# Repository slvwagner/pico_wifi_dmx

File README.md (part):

# pico_wifi_dmx

WiFi-controlled DMX512 controller firmware and browser UI for the Raspberry Pi Pico 2 W (RP2350). Each Pico drives one full 512-channel DMX universe, and one show can combine multiple named Picos as separate DMX outputs/universes. Fixtures are assigned to their output, so the same DMX address can be reused in different universes. The browser can be used for setup and live editing, while chases and effects can also run autonomously on the involved Picos so show playback does not depend on browser timing or WiFi latency.

- **Latest stable release:** `1.3.0`

See [Versioning](#versioning) for the version-number and branch policy and [CHANGELOG.md](CHANGELOG.md) for release notes.

## Getting Started

For a customer PC running 64-bit Windows, download and run the current
**[WiFiPicoDMX 1.3.0 Windows installer](https://github.com/slvwagner/pico_wifi_dmx/releases/download/v1.3.0/wifi-pico-dmx-1.3.0-windows-x64.exe)**.
The installer includes the customer application, local web server, manual, and
guided Pico firmware updater. Because the current installer is unsigned,
Windows can display a SmartScreen publisher warning.

For a 64-bit Ubuntu or Debian computer, download the
**[WiFiPicoDMX 1.3.0 Debian package](https://github.com/slvwagner/pico_wifi_dmx/releases/download/v1.3.0/wifi-pico-dmx_1.3.0_amd64.deb)**
and install it with `sudo apt install ./wifi-pico-dmx_1.3.0_amd64.deb`.

Read the matching
**[WiFiPicoDMX 1.3.0 user manual (PDF)](https://github.com/slvwagner/pico_wifi_dmx/releases/download/v1.3.0/user-manual.pdf)**
for installation, firmware flashing, show setup, and operation instructions.

The [latest GitHub Release](https://github.com/slvwagner/pico_wifi_dmx/releases/latest)
also provides the installer checksum, Pico firmware images, release manifest,
and PDF user manual.

Continue with [Install the Windows customer application](#install-the-windows-customer-application)
for the complete installation, network-access, firmware-update, and startup
instructions.

## Table of Contents

- [Overview](#overview)
- [Critical XAMPP environment safety](#critical-xampp-environment-safety)
- [Customer installation details](#customer-installation-details)
- [Automated Tests](#automated-tests)
- [Project Structure](#project-structure)
- [Versioning](#versioning)
- [Architecture](#architecture)
- [Playback Modes](#playback-modes)
- [HTTP API](#http-api)
- [Web UI](#web-ui)
- [Detailed Source Reference](#detailed-source-reference)
- [Requirements](#requirements)
- [Configure](#configure)
- [Build](#build)
- [Flash](#flash)
- [Resource Usage](#resource-usage)
- [Notes](#notes)

## Overview

The project combines firmware, a XAMPP-hosted web interface, JSON-based setup storage, and automated tests/documentation for a complete small lighting-control workflow.

Core features:

### Show setup and data

- **Fixture Controller** — define fixture profiles, patch one or many fixtures, edit live values, recall Default/Blackout values, create fixture groups, save scenes, and build reusable palettes.
- **Fixture Library** — load fixture profiles from the converted Open Fixture Library catalog with defaults, fine channels, compatible RGB matrices, advanced multi-emitter colors, split-color and filter previews, capability ranges, highlights, and wheel images; merge edited show profiles with reusable library modes in either direction; and export/import the complete catalog as a compressed ZIP.
- **DMX Outputs** — configure multiple named Pico controllers and universes in one show, discover devices on the network, assign every fixture to an output, reuse DMX addresses across universes, and monitor show-wide Pico availability from the shared header.
- **Portable show and library backups** — Fixture Controller provides separate **Export Show**, **Import Show**, **Export Library**, and **Import Library** actions. The show JSON embeds definitions used by its patched fixtures; the compressed library ZIP contains the complete reusable catalog.
- **Server-side JSON data** — setup data is stored under XAMPP `data/*.json`; the complete setup export collects these stores into one portable backup file.

### Programming and visualization

- **Groups and Group Edit** — select fixtures manually or through saved groups, then edit matching controls across mixed fixture types. Optional **Merge Controls** mode combines matching 8-bit/16-bit functions and RGB/RGBW/RGBWA/CMY/CMYK color controls while retaining each fixture's native channels.
- **Scenes and Palettes** — scenes store complete saved looks for their scope; palettes store partial looks such as positions, colors, gobos, dimmer, beam, or fan-out results. Filled tiles can be renamed and styled with a background color plus an optional visual.
- **Fan Out** — shape selected fixtures around snapshotted base values, including Pan/Tilt fan targets, with affected controls highlighted directly in the controller or chaser step editor.
- **Pixel Matrices** — create logical displays up to 64×64 pixels, map each pixel manually or automatically to fixture RGB/RGBW/RGBWA/CMY/CMYK controls or native matrix pixels, and convert uploaded PNG/JPEG/WebP/GIF pictures in the browser with fit and brightness controls. Controller and Show Run recall pictures across the fixtures' assigned DMX Outputs. Chaser can capture pictures as animated steps, preview them on the primary output, and split an autonomous upload into linked Pico payloads.
- **Room Plane** — calibrated room-plane coordinate mapping for moving-light pan/tilt targeting, with a three-point minimum and optional per-fixture accuracy points, saved plane definitions that preserve every point and its calibration, localized triangle interpolation, group selection, and shared Scene/Palette recalls for checking the programmed look while positioning fixtures.

### Playback and live operation

- **Show Run operator page** — arrange Groups, Fixtures, Scenes, Palettes, Pixel Matrices, Room Planes, Live Controls, masters, MIDI, and Pico playback in a configurable card matrix. Operator-critical cards can be moved into a fixed, independently scrolling single-column sidebar with 1–12 configurable rows. The sidebar uses the same visual design and shared adjustable width as the Controller toolbox rail. Card, sidebar, and tile layouts are saved to the server, cards can be repeated for separate operator banks, and the adaptive sticky header keeps navigation visible while reporting show-wide Pico output health.
- **Shared Toolboxes sidebar** — scenes, groups, palettes, fan out, chases, chase steps, playback, effects, and room-plane tools live in a shared resizable sidebar. A common Edit mode enables touch-friendly toolbox and tile reordering plus Cols/Rows selectors, while width, order, collapse state, and group selection are restored consistently across pages.
- **Chaser** — create step-based chases, define participating controls, add/capture/duplicate/reorder steps, recall or edit saved Pixel Matrix pictures directly in the toolbox, preview recalled chases or individual steps on DMX, use browser playback with direction and ping-pong modes, and upload chases into Pico slots for standalone playback.
- **Effects** — apply circle, figure-8, pan swing, tilt swing, sine, and pulse effects to compatible fixture controls. Effects are relative to the current base/scene value and can be saved as reusable recipes or uploaded to Pico effect slots.
- **Pico Playback** — run chaser and effect slots directly on the Pico with play/stop, state-aware pause/resume, direction, loop and ping-pong modes, BPM/speed changes, and slot status readback. Browser, chaser, effect, and manual-recall handoffs stop conflicting playback engines before changing DMX output.
- **MIDI control** — connect a Web MIDI controller or use the Launch Control XL emulator, learn mappings for scenes, live controls, masters, and Pico playback actions, and use soft takeover for continuous controls.
- **GPIO Control** — choose a configured DMX Output and keep independent Pico GPIO mappings per universe for actions such as chase/effect play, stop, pause, resume, speed, BPM, and tap tempo. ADC-capable pins support smoothed analog speed/BPM control; the complete per-output setup autosaves to XAMPP and the selected mapping can be pushed to or read from its Pico.

### Firmware, diagnostics, and development

- **DMX Buffer Monitor** — select a named DMX Output/universe, then read and display its current output buffer or base buffer for all 512 DMX channels.
- **Pico Performance Test** — select one DMX Output or all configured Picos, then verify the installed firmware version, firmware timing, DMX frame health, HTTP callback timing, buffer readback, write throughput, and USB or emulated MIDI-to-DMX response time with per-Pico/universe histories.
- **Controller Pico validation** — the shared header checks every Pico used by the show, reports online coverage and the exact expected firmware version separately, and identifies unreachable, mismatched, or version-less firmware by output name and universe.
- **Partitioned Pico firmware updates** — the application and CYW43 Wi-Fi firmware use separate RP2350 flash partitions, so routine application-only UF2 updates are smaller while release packages retain regular and try-before-you-buy Wi-Fi provisioning images.
- **Release tooling** — scripts safely sync the app to XAMPP, regenerate the dark-mode manual/PDF/screenshots from deterministic data, run isolated UI and optional hardware tests, build firmware, flash the required UF2 files in order, and prepare checksummed release packages.
- **Windows, macOS, and Ubuntu customer installers** — package the app, manual, persistent show storage, a managed web service, native/desktop application launchers, optional trusted-LAN access, upgrade snapshots, and data-preserving uninstall behavior—without shipping MariaDB, phpMyAdmin, or the XAMPP development stack.

License: copying, modification, and sharing are allowed for non-commercial use only. Commercial use requires separate written permission. See [LICENSE](LICENSE).

User-facing operating instructions are in [docs/user-manual.md](docs/user-manual.md). A clean portrait PDF is available at [docs/user-manual.pdf](docs/user-manual.pdf), and a landscape PDF with a persistent clickable contents sidebar is available at [docs/user-manual-navigation.pdf](docs/user-manual-navigation.pdf).

---

## Critical XAMPP environment safety

The two XAMPP applications have different owners and must never be treated as interchangeable:

- `http://<xampp-host>/dmx/` (`<xampp-htdocs>\dmx`) represents the user's working environment. Its `data/*.json` files contain user-owned show data.
- `http://<xampp-host>/dmx-test/` (`<xampp-htdocs>\dmx-test`) represents the automated-test playground. Browser tests may overwrite its JSON data.

These rules are mandatory for developers, scripts, and AI agents:

1. **Never run Playwright, `npm`/`npx` test commands, browser automation, screenshot capture, manual generation, or test diagnostics against `/dmx/`.** Many UI tests intentionally save mock groups, palettes, chases, tile positions, and UI state through the PHP endpoints. A test can destroy live show data even when its assertions look read-only.
2. **Never point `DMX_TEST_BASE_URL`, Playwright `baseURL`, `tests/pathconfig.local.json`, or a temporary test override at `/dmx/`.** The only XAMPP target allowed for automation is `/dmx-test/`. The repository-local PHP server with deterministic `docs/manual-data/` is preferred for manuals and screenshots.
3. **Before starting any browser automation, verify that the target URL path is `/dmx-test/` or a repository-local development server. Stop immediately if it resolves to `/dmx/`.** Do not rely on hostname differences such as `localhost` versus the XAMPP computer's LAN address; the URL path determines the environment.
4. **Deploy source changes to `/dmx/` only with `scripts/update_xampp_server.ps1`.** Do not directly copy, edit, delete, or replace files under `<xampp-htdocs>\dmx`. Use the script with `-AppFolder dmx -BaseUrl http://<xampp-host>/dmx/`, then verify the page manually or with read-only HTTP GET requests.
5. **Use `/dmx-test/` for regression testing.** Synchronize it through `scripts/update_xampp_server.ps1 -AppFolder dmx-test -BaseUrl http://<xampp-host>/dmx-test/` before running tests. Test failures caused by test data must be resolved inside this isolated environment, never by switching the suite to `/dmx/`.
6. **Generate manuals and screenshots outside the user's environment.** Use `scripts/build_user_manual.ps1 -LocalOnly` and the repository's deterministic manual data, or an explicitly isolated test app. Never capture them from `/dmx/`.
7. **Treat XAMPP `data/*.json` as irreplaceable user data.** Do not write, restore, migrate, or import it without explicit user authorization. Before an authorized recovery, snapshot the current files and restore only the files the user approved.
8. **For bug fixes, add and run a failing regression test in the isolated environment before changing implementation code.** After the fix, rerun the focused browser tests there. Run real hardware tests only for firmware changes or when the user explicitly requests them.

The deployment wrapper copies application source and verifies HTTP availability; it is not permission to run tests against the deployed user environment.

---

## Customer installation details

### Install the Windows customer application

For a customer PC, use the generated
`wifi-pico-dmx-<VERSION>-windows-x64.exe` instead of installing the full
XAMPP development stack. The installer:

- installs the customer-facing **WiFiPicoDMX** application below
  `%ProgramFiles%\WiFiPicoDMX` on a new installation (an upgrade can retain
  the earlier program directory);
- stores mutable shows and fixture data in the upgrade-compatible location
  `%ProgramData%\Pico DMX Controller\data`;
- starts the `PicoDmxController` Windows service automatically;
- creates Start Menu and desktop shortcuts that open a dedicated native
  application window, with the default browser as fallback;
- lets the customer choose an available HTTP port, defaulting to 8090, and
  remembers that choice during upgrades;
- identifies an already running Pico DMX installation on that port and asks to
  close its window/service so upgrades can retain the same address;
- optionally enables the selected TCP port on the Windows **Private** firewall
  profile so iPads and other trusted LAN devices can connect;
- asks whether to open the guided Pico firmware installer after setup and
  bundles the matching application UF2, Wi-Fi UF2, checksum manifest, and
  Raspberry Pi `picotool`;
- snapshots existing data before an upgrade and preserves all `ProgramData`
  when the software is uninstalled.

Keep the Private-network option disabled when the controller will be used only
on the Windows PC. Enable it when an iPad or another operator device must open
`http://<controller-pc-address>:<selected-port>/`. Do not expose the selected
port to the public internet.

The installer source and reproducible build instructions are in
[`installer/windows/README.md`](installer/windows/README.md). Customer release
builds should be Authenticode-signed; unsigned development builds can trigger a
Windows SmartScreen warning.

Firmware flashing is opt-in and occurs only in the WiFiPicoDMX guide after
installation. Before BOOTSEL, **Check installed firmware** reuses the
Controller's Pico discovery service to find every running Pico on the network
and compare its reported version with the validated bundled firmware. The
guide then explains how to connect exactly one Pico 2 W in BOOTSEL mode,
validates the bundled files and target, asks again before writing, prevents
closing during the flash, and reports recovery steps. The guide can set or
change the Pico's Wi-Fi network name and password without storing them in the
installer or application firmware; later firmware-only updates preserve that
separate configuration. It can also be opened
later through **Application > Firmware update…** or the Start Menu **Firmware
Update** shortcut.

The native **WiFiPicoDMX** application window provides normal minimize/maximize/close controls,
F11 fullscreen, Escape to leave fullscreen, and Open/fullscreen/exit actions
from its tray icon. Its Windows title bar/frame, menu and dropdown surfaces,
status bar, tray menu, and fullscreen controls use a matching dark theme.
Fullscreen retains a small bar with **Exit full screen** and **Close
application**, so it never traps the operator in kiosk mode. Closing the GUI
offers **Exit only**, **Exit and stop server**, and **Cancel**. Exit only closes
the local window while keeping the server available to iPads and other PCs.
Exit and stop server requests Windows administrator approval, stops the
`PicoDmxController` service, and then exits. While Windows completes the
shutdown, a non-dismissible progress window remains visible and explains that
the operation can take up to 45 seconds. The shell performs a final service
state check before reporting a failure. Cancelling leaves the application and
server running.
When the shortcut is opened after such a shutdown, the shell explains that
administrator approval is required, starts the stopped service, and then loads
the controller. No approval prompt is shown when the service is already
running. Before loading the interface, the native application clears only its
WebView2 disk cache and the packaged server requires changed HTML, CSS, and
JavaScript to be revalidated. This prevents an upgraded installation from
showing an older layout while preserving show data, browser-local settings,
and cookies.

### Install the macOS customer application

Build the architecture-specific macOS package on macOS 12 or newer:

```bash
./installer/macos/build_php_runtime.sh
./installer/macos/build_package.sh
```

Open the generated
`wifi-pico-dmx-<VERSION>-macos-<ARCH>.pkg`, then start **WiFiPicoDMX** from
Applications. Its native dark WKWebView window supplies
Controller Settings, reload, normal macOS fullscreen, and standard close/quit
actions. First-run setup accepts an available HTTP port from `1024–65535`
(default `8090`) and keeps access local unless the customer explicitly enables
trusted-LAN access.

The app installs its own per-user LaunchAgent. Closing or quitting offers
**Exit only**, **Exit and stop server**, and **Cancel**. Exit only keeps the
server available to operator devices; Exit and stop server unloads only that
LaunchAgent. The upgrade-compatible app bundle and show-data paths remain
under `/Applications/Pico DMX Controller.app` and
`~/Library/Application Support/Pico DMX Controller`. Removing the app therefore
does not silently remove shows.

The package source, pinned standalone-PHP build, Developer ID signing, Apple
notarization, stapling, and customer instructions are documented in
[`installer/macos/README.md`](installer/macos/README.md). Build customer
releases with organization-owned **Developer ID Application** and **Developer
ID Installer** identities and a protected Keychain notarization profile.

### Install the Ubuntu customer application

Build the Ubuntu package on Ubuntu or Debian:

```bash
./installer/ubuntu/build_package.sh
```

On Windows, the PowerShell wrapper runs the same package builder inside WSL 2,
so the Windows and Debian installers can be produced from one checkout:

```powershell
.\installer\ubuntu\build_package_wsl.ps1 -Distribution Ubuntu-24.04
```

WSL must contain a Linux `picotool` 2.3.0 build because that executable is
included in the Debian package. If it is outside the normal
`~/.pico-sdk/picotool/2.3.0/picotool/picotool` location, pass its Linux path
with `-WslPicotoolPath`.

Install the generated package from `release/v<VERSION>/` by double-clicking it
in Ubuntu's App Center, or with APT:

```bash
sudo apt install ./wifi-pico-dmx_<VERSION>_amd64.deb
```

The package installs the read-only application below
`/opt/pico-dmx-controller`, stores mutable shows and fixture data below
`/var/lib/pico-dmx-controller/data`, manages its systemd service with the app,
and adds **WiFiPicoDMX** to the Applications menu. The self-contained
application includes its own Chromium engine, dark frame, application and
fullscreen controls, status bar, tray menu, and Web MIDI support. The installer
also creates an executable shortcut on normal users' configured XDG desktops
without replacing unrelated files. The service listens only on
`127.0.0.1:8090` by default. Launching the application starts that service.
Closing offers **Exit only**, **Exit and stop server**, and **Cancel**; Exit
only leaves PHP available to operator devices, while Exit and stop server
stops it after all local WiFiPicoDMX windows have closed.

To allow iPads and other operator devices on a trusted local network, run:

```bash
sudo pico-dmx-config --lan
```

This changes the listener to all network interfaces and adds the packaged TCP
8090 UFW rule when UFW is active. Return to local-only access with
`sudo pico-dmx-config --local`. Do not expose port 8090 to the public internet.
Upgrades snapshot current show data, and removing the package preserves all
data under `/var/lib/pico-dmx-controller`.

Application-managed startup remains the default. Installations that must start
the server automatically at boot can opt in with
`sudo pico-dmx-config --always-on`; restore application-managed startup with
`sudo pico-dmx-config --application-managed`.

The package source, behavior, and build instructions are documented in
[`installer/ubuntu/README.md`](installer/ubuntu/README.md).

### Run the developer XAMPP environment

Install the runtime tools:

- **XAMPP for Windows** with Apache and PHP enabled. The browser UI uses PHP files in `api/` to save JSON setup data.
- A modern browser such as Chrome, Edge, or Safari.
- A Raspberry Pi Pico 2 W flashed with the `pico_wifi_dmx` firmware.

Configure the local paths first. The scripts use `config/local-paths.json` as their default path configuration for your machine:

```powershell
cd <path-to-your-checkout>\pico_wifi_dmx
Copy-Item config\local-paths.example.json config\local-paths.json
```

Edit `config/local-paths.json` so it matches your XAMPP installation, app folder, browser URL, and Chrome path:

```json
{
  "xamppHtdocs": "C:/path/to/xampp/htdocs",
  "appFolder": "dmx",
  "baseUrl": "http://localhost/dmx/",
  "chromePath": "C:/Program Files/Google/Chrome/Application/chrome.exe"
}
```

These values mean the web app will be copied to:

```text
<XAMPP installation directory>\htdocs\<app folder>\
```

`config/local-paths.json` is ignored by Git. Keep your real machine paths there. The sync, manual screenshot/PDF, README screenshot, and release helper scripts read this file automatically. If you pass path parameters directly to a script, those command-line values override the config file for that run.

Copy the web app to XAMPP:

```powershell
.\scripts\sync_fixture_controller_to_xampp.ps1
```

Or use the deployment wrapper, which syncs the app and verifies the deployed pages:

```powershell
.\scripts\update_xampp_server.ps1
```

Open the UI:

```text
http://localhost/dmx/
```

On Ubuntu, you can run the browser UI directly from the repository without XAMPP:

```bash
cd ~/pico_wifi_dmx
php -S 127.0.0.1:8000 tools/local-server/router.php
```

Then open:

```text
http://127.0.0.1:8000/
```

If port `8000` is already in use, choose another port in both commands, for example `8002`.

The built-in PHP server stores setup JSON under `api/data/`. This is local runtime data and is ignored by Git.

`127.0.0.1` is only reachable from the same Ubuntu machine. To use the UI from another device on the network, deploy it into XAMPP instead. On Ubuntu XAMPP installs commonly live under `/opt/lampp`; this project can use the PowerShell deployment wrapper:

```bash
pwsh -NoProfile -ExecutionPolicy Bypass \
  -File scripts/update_xampp_server.ps1 \
  -XamppHtdocs /opt/lampp/htdocs \
  -AppFolder dmx \
  -BaseUrl http://localhost/dmx/
```

If your XAMPP `htdocs` root is not writable by your user, deploy under a writable subfolder, for example:

```bash
pwsh -NoProfile -ExecutionPolicy Bypass \
  -File scripts/update_xampp_server.ps1 \
  -XamppHtdocs /opt/lampp/htdocs/editable \
  -AppFolder dmx \
  -BaseUrl http://localhost/editable/dmx/
```

After `config/local-paths.json` contains the Ubuntu paths, updating this machine's XAMPP copy is just:

```bash
pwsh -NoProfile -ExecutionPolicy Bypass -File scripts/update_xampp_server.ps1
```

Then open the matching URL from the Ubuntu machine, or replace `localhost` with the Ubuntu machine's LAN IP from another device. The XAMPP URL is only the address of the web interface and server-side show storage; it is independent from the Pico URLs assigned to the show's DMX Outputs.

Configure hardware from **Fixture Controller → DMX Outputs**. Use **Find Picos** to receive every Pico discovery beacon on UDP port `64540`, then add the wanted devices and assign their universes. Each beacon includes the Pico SDK unique-board ID, which the show stores as the output's stable device identity independently of its DHCP address. If the same Pico later advertises a different IP address, **Find Picos** automatically updates only its saved URL. The output ID, universe, name, fixture assignments, and all show programming stay unchanged; click **Done** to autosave the refreshed address. URLs can also be entered manually in that modal. The sticky header on every page checks the outputs used by patched fixtures and shows **online/total Picos online**; click the pill to refresh immediately. Green means every used output answered, amber means only some answered, and red means none answered. On the Fixture Controller, **DMX Outputs** remains anchored at the right edge of the status row while this text refreshes; when horizontal space is constrained, the fleet text is shortened with an ellipsis instead of wrapping or moving the button.

Changing IP numbers are handled in two places:

- **XAMPP/server URL**: configure scripts and tests with `config/local-paths.json`, `tests/pathconfig.local.json`, or `DMX_TEST_BASE_URL`. The browser app itself uses relative URLs for setup files, so once a page is opened from the right XAMPP address it continues to talk to the same server.
- **Pico URLs**: configure show hardware with Controller → **DMX Outputs**. Run **Find Picos** after a DHCP change; a Pico whose saved unique-board ID is recognized receives its current URL automatically. Hardware tests may still override their target with `DMX_PICO_BASE_URL`.

Setup data is saved in XAMPP under `dmx/data/*.json`. Use **Fixture Controller > Show > Export Show** before large changes when you want an extra backup of the complete show setup, including named DMX Outputs/universes, fixture output assignments, and every Pico's GPIO/ADC mappings.

### Install the firmware

Committed firmware releases are stored in:

```text
release/v<VERSION>/pico_wifi_dmx-v<VERSION>.uf2
```

Use that application UF2 when the separate Wi-Fi firmware partition has already been provisioned and you do not need to build from source. To update it:

1. Hold the Pico 2 W **BOOTSEL** button while plugging it into USB.
2. Wait for the `RPI-RP2` drive to appear.
3. Copy `release/v<VERSION>/pico_wifi_dmx-v<VERSION>.uf2` to that drive.
4. The Pico reboots automatically.
5. Open the serial log and note the printed Pico URL.

The matching checksum is stored beside it in:

```text
release/v<VERSION>/pico_wifi_dmx-v<VERSION>.uf2.sha256
```

Release 0.9.10 is the final single-UF2 release. Starting with 0.9.11, the CYW43 Wi-Fi firmware is stored in its own RP2350 flash partition. A new device, or a device upgrading from 0.9.10 or older, must receive both of these files once:

```text
release/v<VERSION>/pico_wifi_dmx-v<VERSION>.uf2
release/v<VERSION>/pico_wifi_dmx-wifi-firmware-v<VERSION>.uf2
```

Flash the application UF2 first so it installs the partition table, enter USB boot mode again, and then flash the Wi-Fi firmware UF2. With picotool:

```powershell
$Picotool = "$env:USERPROFILE/.pico-sdk/picotool/2.3.0/picotool/picotool.exe"
& $Picotool load release/v<VERSION>/pico_wifi_dmx-v<VERSION>.uf2
& $Picotool reboot -u
& $Picotool load -ux release/v<VERSION>/pico_wifi_dmx-wifi-firmware-v<VERSION>.uf2
```

After that one-time provisioning, normal application updates require only `pico_wifi_dmx-v<VERSION>.uf2`. Reflash the separate Wi-Fi firmware only when a release explicitly says that its CYW43 firmware changed. The release also contains a `-tbyb` Wi-Fi UF2 for advanced RP2350 try-before-you-buy updates; it is not needed for a normal initial installation. If no prebuilt UF2 is available, build it from source with the developer steps below.

Windows customer installations can perform the complete two-file procedure
through **Application > Firmware update…** without installing developer tools.

### Build the firmware from source

This project was created around the official Raspberry Pi Pico development environment for Visual Studio Code. The checked-in configuration targets:

| Component | Project configuration |
| --- | --- |
| Board | Raspberry Pi Pico 2 W (`pico2_w`, RP2350) |
| Pico SDK | 2.3.0 |
| ARM GNU Toolchain | 14.2.Rel1 |
| picotool | 2.3.0 |
| CMake | 3.31.5 |
| Ninja | 1.12.1 |
| OpenOCD | 0.12.0+dev |

Install [Visual Studio Code](https://code.visualstudio.com/) and open the repository as a single-folder workspace. VS Code reads [`.vscode/extensions.json`](.vscode/extensions.json) and offers to install the extensions used by this project:

| Marketplace extension | ID | Used here for |
| --- | --- | --- |
| [Raspberry Pi Pico](https://marketplace.visualstudio.com/items?itemName=raspberry-pi.raspberry-pi-pico) | `raspberry-pi.raspberry-pi-pico` | Official Pico SDK/toolchain management, CMake configuration, compilation, target selection, flashing, and debug commands |
| [C/C++](https://marketplace.visualstudio.com/items?itemName=ms-vscode.cpptools) | `ms-vscode.cpptools` | C/C++ IntelliSense, code navigation, and `compile_commands.json` integration |
| [C/C++ Extension Pack](https://marketplace.visualstudio.com/items?itemName=ms-vscode.cpptools-extension-pack) | `ms-vscode.cpptools-extension-pack` | Installs the broader Microsoft C/C++ environment, including CMake Tools |
| [Cortex-Debug](https://marketplace.visualstudio.com/items?itemName=marus25.cortex-debug) | `marus25.cortex-debug` | RP2350 GDB debugging through OpenOCD, including the supplied internal and external OpenOCD launch profiles |
| [Serial Monitor](https://marketplace.visualstudio.com/items?itemName=ms-vscode.vscode-serial-monitor) | `ms-vscode.vscode-serial-monitor` | Viewing Pico boot, network, and diagnostic output over USB serial |

The repository configuration supplies the matching environment paths on Windows, Linux, and macOS. It also provides VS Code tasks for **Compile Project**, picotool **Run Project**, OpenOCD **Flash**, **Rescue Reset**, and **RISC-V Reset (RP2350)**. The Raspberry Pi Pico extension is the simplest way to install or locate the pinned SDK, compiler, CMake, Ninja, picotool, and OpenOCD versions; if prompted by CMake Tools, select the supplied **Pico** kit.

Configure and build:

```powershell
cd <path-to-your-checkout>\pico_wifi_dmx
cmake -S . -B build -G Ninja
cmake --build build
```

On Ubuntu, use the same commands:

```bash
cd ~/pico_wifi_dmx
cmake -S . -B build -G Ninja
cmake --build build
```

Wi-Fi credentials are intentionally not accepted as CMake options or compiled
into the application UF2. Set them while flashing with the Windows/Ubuntu
firmware updater. They are written to a dedicated 16 KB data partition, which
normal application updates leave intact.

Legacy `SSID` and `SSID_PW` environment variables are ignored by both the
firmware build and the Windows application. The updater uses the values entered
in its Wi-Fi fields and passes them to the flashing helper through temporary
`PICO_DMX_WIFI_*` child-process variables. Those internal variables are cleared
before `picotool` starts and are not a supported configuration interface.

If CMake cannot find the Pico SDK, install the Raspberry Pi Pico VS Code extension on Ubuntu or point CMake at an SDK checkout:

```bash
export PICO_SDK_PATH="$HOME/.pico-sdk/sdk/2.3.0"
```

The firmware output is:

```text
build/pico_wifi_dmx.uf2
```

Optional firmware settings:

```powershell
-DDMX_TX_PIN=2 -DDMX_TRIGGER_PIN=3
-DDMX_CHANNELS=512
-DMIDI_ENABLED=1 -DMIDI_RX_PIN=5 -DMIDI_UART_ID=1 -DMIDI_BAUD=31250
```

Default hardware wiring:

```text
Pico GPIO2 -> RS-485/DMX driver DI input
Pico GPIO5 -> MIDI input receiver UART output
Pico GND   -> RS-485/DMX driver GND
Pico 3V3   -> RS-485/DMX driver VCC, if the module supports 3.3 V
Driver D+  -> DMX XLR pin 3
Driver D-  -> DMX XLR pin 2
Shield/GND -> DMX XLR pin 1
```

Do not connect Pico GPIO2 directly to a DMX cable. DMX uses an RS-485 differential line, so the Pico output must go through a suitable RS-485/DMX line driver. GPIO3 is only the optional frame-trigger/debug pin, not a DMX data output. GPIO5 is reserved by default as the DIN/TRS MIDI receive input (`MIDI_RX_PIN=5`, `MIDI_UART_ID=1`). Feed GPIO5 only from a proper MIDI input receiver/opto-isolation circuit; do not wire a MIDI connector directly to the Pico GPIO.

### Rev. A Fusion hardware design

The Rev. A carrier schematic, PCB starting layout, physical net lists, and
design-specific component library are generated as compatible EAGLE XML files
for Fusion Electronics. Regenerate the complete bundle in dependency order:

```powershell
node scripts/generate_fusion_schematic.mjs
node scripts/generate_fusion_used_library.mjs
node scripts/generate_fusion_board.mjs
```

The bundle places these uploadable design files together:

- `hardware/fusion/WiFiPicoDMX_RevA.sch`;
- `hardware/fusion/WiFiPicoDMX_RevA.brd`;
- `hardware/fusion/WiFiPicoDMX_RevA_used.lbr`.

The schematic generator defines component/pad mappings, named signals and
connections once. The board generator preserves the reviewed 95 mm × 100 mm
functional placement, four ground pours, and DMX/MIDI isolation restrictions.
The used-library generator filters the schematic to the exact symbols,
packages, device sets, and available 3D associations present in Rev. A.

The schematic and board use the same `WiFiPicoDMX_RevA_used` library identity
as the standalone `.lbr`. EAGLE/Fusion still embeds the used definitions in
each design file so the pair remains portable; uploading the `.lbr` separately
makes the same components reusable and permits a deliberate **Swap Library**
to a managed Fusion library.

Run the structural hardware regression suite after regeneration:

```powershell
node --test tests/hardware/*.test.mjs
```

The generated design is an engineering prototype and still requires Fusion
ERC/DRC, `RATSNEST` review, manufacturer land-pattern verification, isolation
review, routing, and mechanical checking before PCB fabrication. See
[`hardware/fusion/README.md`](hardware/fusion/README.md) for the complete
generation/import workflow, output ownership, expected counts, and review
requirements.

DMX signal generation and timing:

| Signal part | Value |
| --- | --- |
| Output method | PIO control state machine + PIO data state machine + DMA |
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
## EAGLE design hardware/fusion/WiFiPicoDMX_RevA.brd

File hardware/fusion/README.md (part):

# Fusion Electronics files

`WiFiPicoDMX_RevA.sch` is a self-contained Autodesk EAGLE XML schematic that
can be uploaded to Autodesk Fusion Electronics. EAGLE stores the component
definitions and land patterns used by a design inside its schematic and board
files. Those embedded records use the `WiFiPicoDMX_RevA_used` library identity,
matching the standalone `WiFiPicoDMX_RevA_used.lbr` supplied beside the design.

The maintained Fusion/EAGLE source library is
[`libraries/WiFiPicoDMX.lbr`](libraries/WiFiPicoDMX.lbr). The generator reads
that file directly and imports the matching land patterns for the Pico 2 W,
resistors, capacitors, ferrites, LEDs, reset switch, PPTC fuse, ISOW1412,
SM712, ACT45B, HCPL-0700, 1N4148WS, and the available diagnostic pad banks. If
the library file is missing or one of those package names is removed,
generation stops instead of silently falling back to another footprint.

## Design bundle and file ownership

| File | Role | Edit policy |
|---|---|---|
| `WiFiPicoDMX_RevA.sch` | Three-sheet schematic with embedded used-component records | Generated; edit `scripts/generate_fusion_schematic.mjs` |
| `WiFiPicoDMX_RevA.brd` | 95 mm × 100 mm PCB starting layout with placement, restrictions, and ground polygons | Generated; edit `scripts/generate_fusion_board.mjs` |
| `WiFiPicoDMX_RevA_used.lbr` | Exact standalone library subset used by the design | Generated; edit the maintained library/generator inputs |
| `WiFiPicoDMX_RevA_netlist.csv` | One row per physical electrical connection | Generated with the schematic |
| `WiFiPicoDMX_RevA_netlist.md` | Human-readable nets, references, values, and review notes | Generated with the schematic |
| `libraries/WiFiPicoDMX.lbr` | Maintained source footprint/symbol library | Source file; do not replace it with the generated subset |

The schematic contains 40 part records: 37 physical components and three A3
sheet frames. The board contains the same 37 physical components and 55 named
nets. The generated used library currently contains 20 device sets, 17
symbols, 19 packages, and eight available 3D associations. These counts are
asserted by the hardware tests and must be reviewed if the design changes.

## How the schematic is created

The schematic was not drawn manually in Fusion. EAGLE `.sch` files use an XML
format that Fusion Electronics can import, so
[`scripts/generate_fusion_schematic.mjs`](../../scripts/generate_fusion_schematic.mjs)
builds the file programmatically.

The generator is the single source for:

- schematic symbols and symbolic pin names;
- the selection of package footprints and physical pad numbers;
- component references, values and sheet positions;
- physical pin-to-pad mappings;
- named signals and their connected endpoints;
- the EAGLE XML schematic and both net-list formats.

The project library is the source for the imported land-pattern geometry.
See [`libraries/README.md`](libraries/README.md) for the import list and the
footprints deliberately retained as project-specific definitions.

The generator also copies every available `packages3d` model and
device-to-model association for packages actually used by the schematic.
Unused library models are intentionally omitted from the self-contained
schematic. A corrected custom footprint is left without a 3D model when the
library contains no dimensionally correct model for it; the generator never
reuses a model belonging to the former, incorrect package.

For example, one `connectMany()` declaration connects the Pico DMX output,
ISOW1412 data input, pull-up resistor and diagnostic pad to the named
`DMX_TX_GPIO2` signal. The generator translates that declaration into EAGLE
XML net segments and also writes the corresponding physical endpoints into
the CSV and Markdown net lists. This prevents the three generated files from
having separately maintained connection data.

The generator validates that every referenced component and symbolic pin has
a physical package-pad mapping before writing the files. XML and endpoint
count checks should still be run after generation. This structural validation
does not certify the circuit or its footprints.

For redrawing or independently reviewing the circuit:

- `WiFiPicoDMX_RevA_netlist.csv` contains one row per physical connection;
- `WiFiPicoDMX_RevA_netlist.md` groups the same physical endpoints by net and
  includes the reference/value table and critical review notes.

Regenerate the schematic and both net lists from the repository root with:

```powershell
node scripts/generate_fusion_schematic.mjs
node scripts/generate_fusion_used_library.mjs
```

Expected output:

- `hardware/fusion/WiFiPicoDMX_RevA.sch`;
- `hardware/fusion/WiFiPicoDMX_RevA_used.lbr`;
- `hardware/fusion/WiFiPicoDMX_RevA_netlist.csv`;
- `hardware/fusion/WiFiPicoDMX_RevA_netlist.md`.

## Importing the bundle into Fusion

Keep the `.sch`, `.brd`, and `.lbr` together when uploading or archiving the
design:

1. upload `WiFiPicoDMX_RevA.sch` and `WiFiPicoDMX_RevA.brd` as the matching
   schematic/board pair;
2. upload `WiFiPicoDMX_RevA_used.lbr` to the same Fusion project when the
   components should also be available for reuse;
3. open the design pair and confirm that all parts/elements identify
   `WiFiPicoDMX_RevA_used`;
4. if a managed Fusion library relationship is required, import the `.lbr`,
   mark it **In Use**, and deliberately use **Swap Library** after verifying
   that every device and variant matches;
5. run ERC, calculate the board with `RATSNEST *;`, and run DRC before making
   any manufacturing output.

The `<libraries>` sections inside `.sch` and `.brd` are expected. EAGLE stores
the used component definitions inside each drawing for portability. Their
presence does not mean that the standalone library is ignored: the embedded
records and every part/element reference now share the external library's
`WiFiPicoDMX_RevA_used` base name. Fusion may assign a hub URN when converting
the local `.lbr`; use **Swap Library** rather than editing XML identifiers by
hand.

## Basic carrier-board layout

`WiFiPicoDMX_RevA.brd` is a basic, deliberately unrouted two-layer carrier
layout generated from the schematic and physical net list. Regenerate it
after regenerating the schematic:

```powershell
node scripts/generate_fusion_schematic.mjs
node scripts/generate_fusion_used_library.mjs
node scripts/generate_fusion_board.mjs
```

The starter layout provides:

- all 37 physical components and all 55 named airwire nets;
- a plain rectangular 95 mm × 100 mm board outline matching the first
  manually arranged Fusion layout, without enclosure-specific mounting holes;
- the complete Pico 2 W development board mounted through the two 20-pin
  header rows from the supplied library footprint, without a carrier cutout
  or Pico-specific keepout/access zone;
- free GPIO and analog pad banks to the left of the centrally placed Pico;
- an upper DMX signal path running left to right from the Pico, through the
  ISOW1412 and line protection, to the panel-harness connector;
- a local top, bottom, and via restrict corridor beneath the upper ISOW1412
  isolation barrier;
- a lower MIDI signal path running left to right from the panel-harness
  connector and protected input network, through the HCPL-0700, to the Pico;
- a board-edge MIDI input island enclosed by the carrier edges and top,
  bottom, and via-restrict moats, with the HCPL-0700 straddling its boundary;
- top- and bottom-layer polygon pours for `GND_LOGIC` and `GND_DMX_ISO`,
  matching the manually arranged Fusion layout;
- a locally routed `GND_DMX_CONVERTER` return without a polygon so the FB2
  high-frequency filtering boundary remains effective;
- one shared conservative default net class for clean Fusion
  schematic/board import consistency.

The generated placement is an engineering starting point, not an autorouted
or production-ready PCB. Fusion must still be used to review the mechanical
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
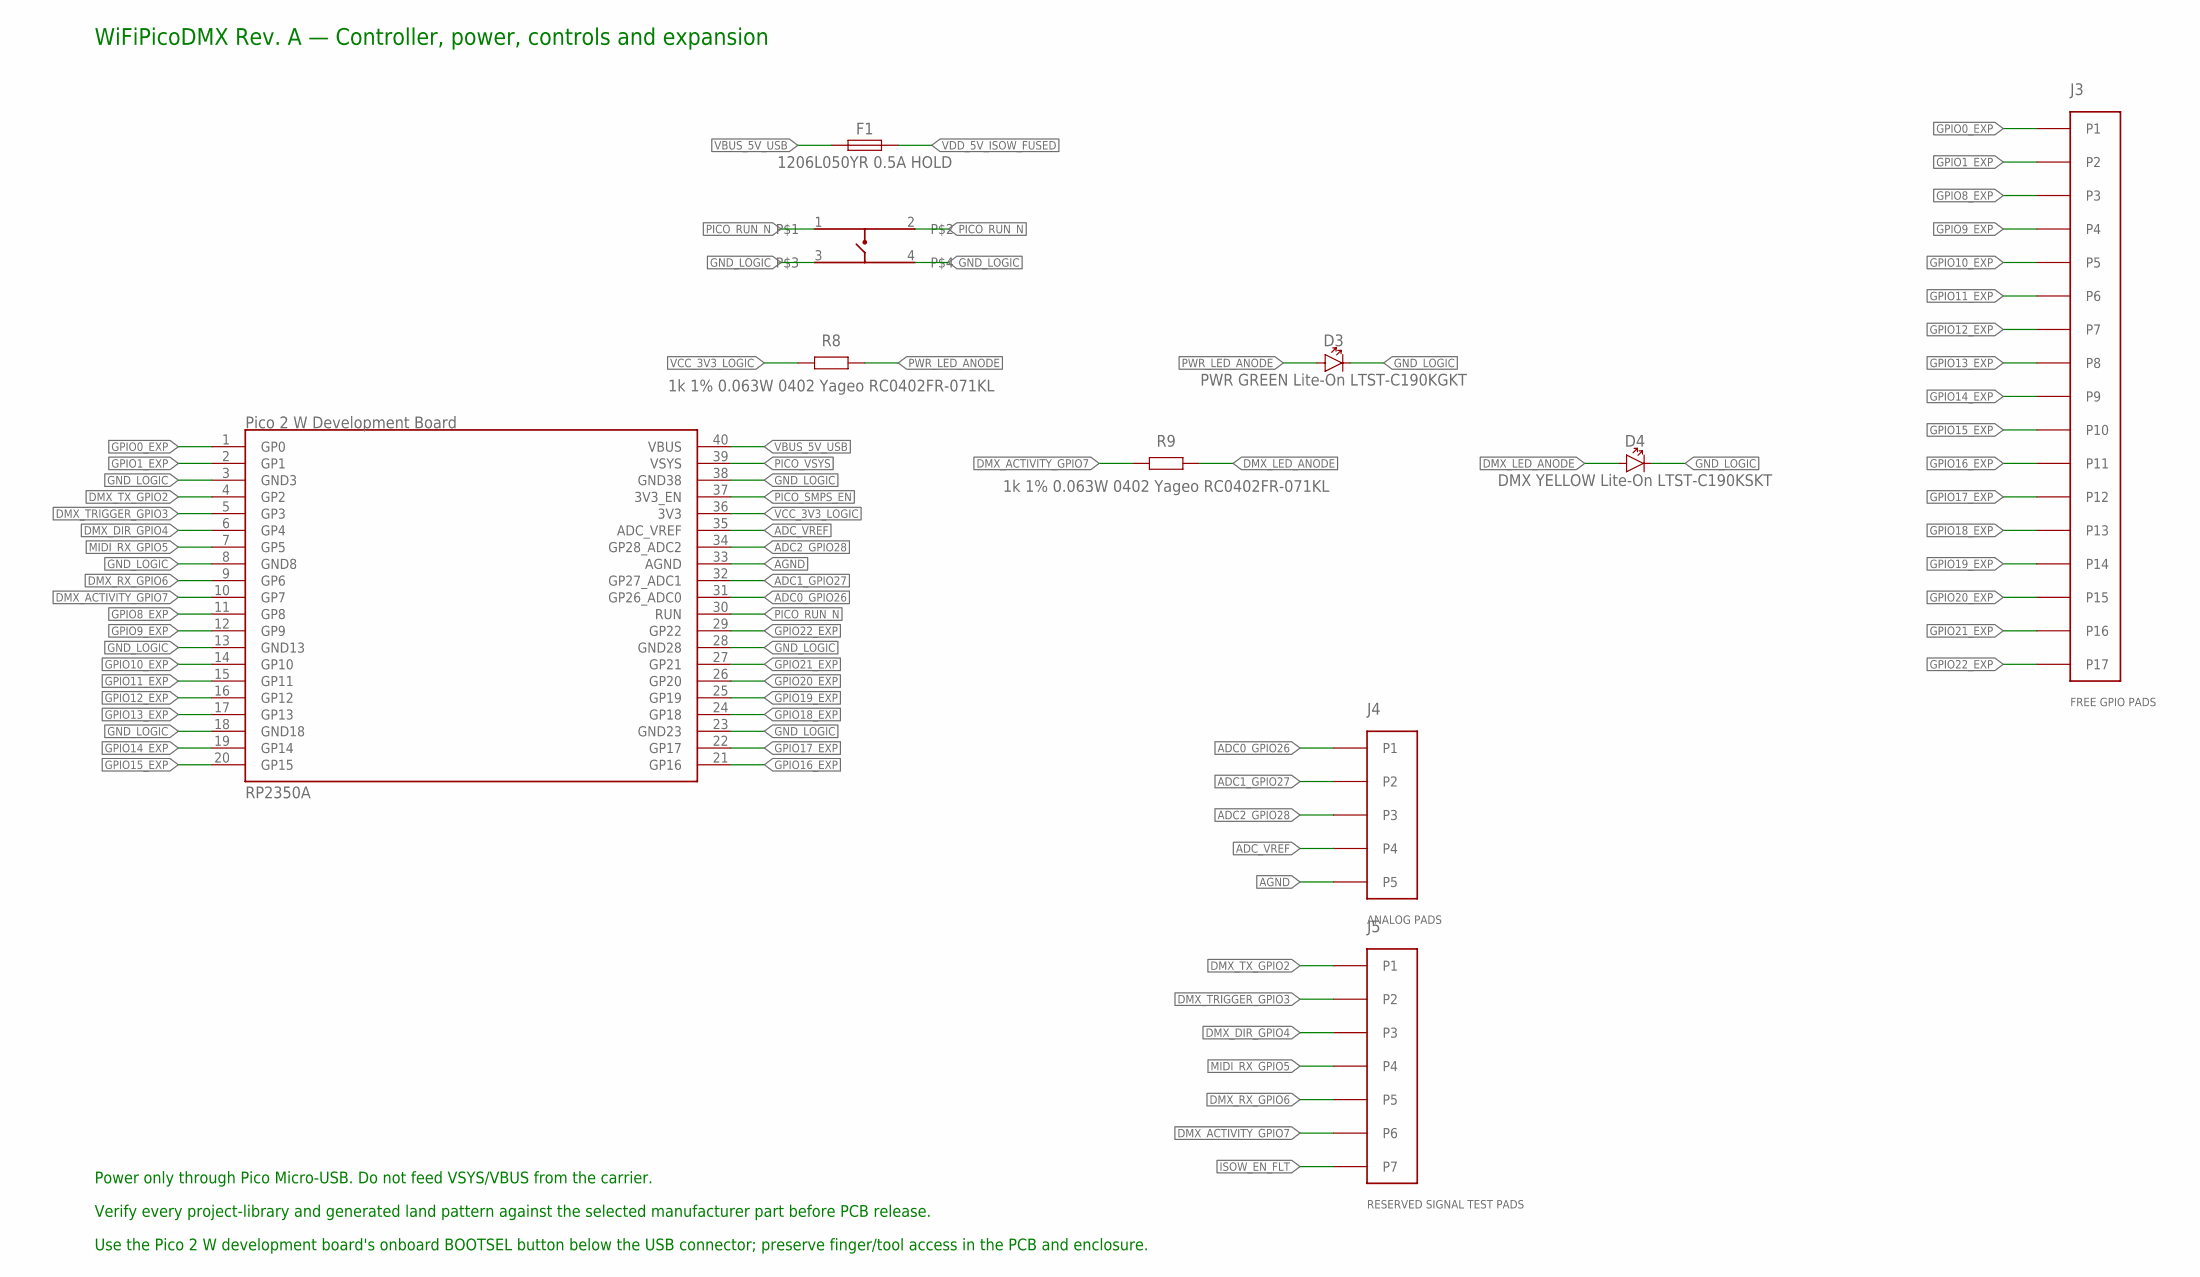
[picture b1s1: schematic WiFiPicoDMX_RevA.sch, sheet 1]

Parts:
D3: PWR GREEN Lite-On LTST-C190KGKT; LEDC1608X55N_FLAT-B
D4: DMX YELLOW Lite-On LTST-C190KSKT; LEDC1608X55N_FLAT-B
F1: 1206L050YR 0.5A HOLD; PPTC1206_1206L050YR
J3: FREE GPIO PADS; PADBANK17
J4: ANALOG PADS; PADBANK5
J5: RESERVED SIGNAL TEST PADS; PADBANK7
R8, R9: 1k 1% 0.063W 0402 Yageo RC0402FR-071KL; RESC1005X40
SW1: PTS810SJM250SMTR LFS RESET (NO); PTS810_J_LEAD
U1: Raspberry Pi Pico 2 W; PICO_2_W_DEVELOPMENT_BOARD

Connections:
ADC0_GPIO26: J4.1, U1.31 (GP26_ADC0)
ADC1_GPIO27: J4.2, U1.32 (GP27_ADC1)
ADC2_GPIO28: J4.3, U1.34 (GP28_ADC2)
ADC_VREF: J4.4, U1.35 (ADC_VREF)
AGND: J4.5, U1.33 (AGND)
DMX_ACTIVITY_GPIO7: J5.6, R9.1, U1.10 (GP7)
DMX_DIR_GPIO4: J5.3, U1.6 (GP4); also elsewhere on the board
DMX_LED_ANODE: D4.A, R9.2
DMX_RX_GPIO6: J5.5, U1.9 (GP6); also elsewhere on the board
DMX_TRIGGER_GPIO3: J5.2, U1.5 (GP3)
DMX_TX_GPIO2: J5.1, U1.4 (GP2); also elsewhere on the board
GND_LOGIC: D3.C (K), D4.C (K), SW1.3, SW1.4, U1.3 (GND3), U1.8 (GND8), U1.13 (GND13), U1.18 (GND18), U1.23 (GND23), U1.28 (GND28), U1.38 (GND38); also elsewhere on the board
GPIO0_EXP: J3.1, U1.1 (GP0)
GPIO1_EXP: J3.2, U1.2 (GP1)
GPIO8_EXP: J3.3, U1.11 (GP8)
GPIO9_EXP: J3.4, U1.12 (GP9)
GPIO10_EXP: J3.5, U1.14 (GP10)
GPIO11_EXP: J3.6, U1.15 (GP11)
GPIO12_EXP: J3.7, U1.16 (GP12)
GPIO13_EXP: J3.8, U1.17 (GP13)
GPIO14_EXP: J3.9, U1.19 (GP14)
GPIO15_EXP: J3.10, U1.20 (GP15)
GPIO16_EXP: J3.11, U1.21 (GP16)
GPIO17_EXP: J3.12, U1.22 (GP17)
GPIO18_EXP: J3.13, U1.24 (GP18)
GPIO19_EXP: J3.14, U1.25 (GP19)
GPIO20_EXP: J3.15, U1.26 (GP20)
GPIO21_EXP: J3.16, U1.27 (GP21)
GPIO22_EXP: J3.17, U1.29 (GP22)
ISOW_EN_FLT: J5.7; also elsewhere on the board
MIDI_RX_GPIO5: J5.4, U1.7 (GP5); also elsewhere on the board
PICO_RUN_N: SW1.1, SW1.2, U1.30 (RUN)
PICO_SMPS_EN: U1.37 (3V3_EN)
PICO_VSYS: U1.39 (VSYS)
PWR_LED_ANODE: D3.A, R8.2
VBUS_5V_USB: F1.1, U1.40 (VBUS); also elsewhere on the board
VCC_3V3_LOGIC: R8.1, U1.36 (3V3); also elsewhere on the board
VDD_5V_ISOW_FUSED: F1.2; also elsewhere on the board

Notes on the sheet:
WiFiPicoDMX Rev. A — Controller, power, controls and expansion
Power only through Pico Micro-USB. Do not feed VSYS/VBUS from the carrier.
Verify every project-library and generated land pattern against the selected manufacturer part before PCB release.
Use the Pico 2 W development board's onboard BOOTSEL button below the USB connector; preserve finger/tool access in the PCB and enclosure.

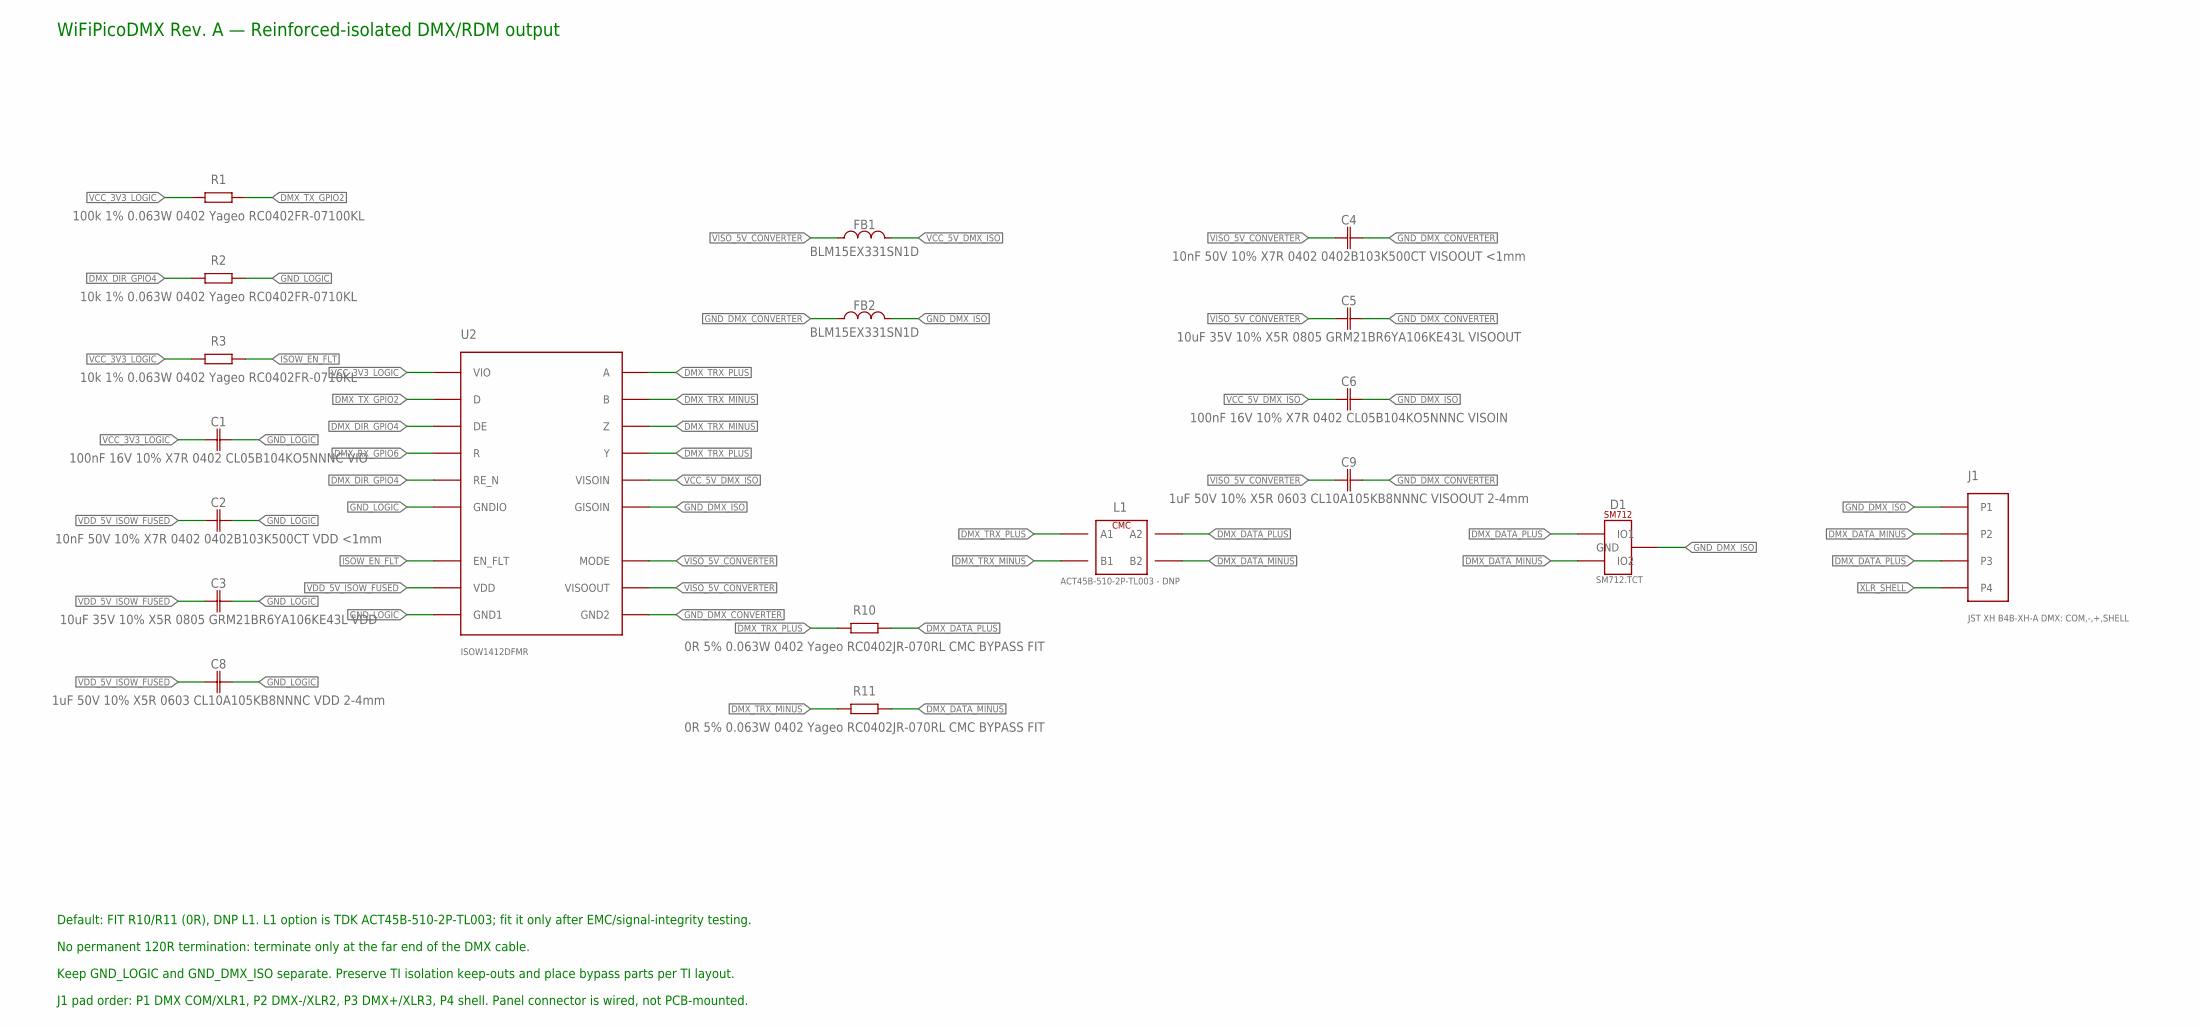
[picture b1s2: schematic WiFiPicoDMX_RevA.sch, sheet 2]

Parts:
C1: 100nF 16V 10% X7R 0402 CL05B104KO5NNNC VIO; CAPC1005X60
C2: 10nF 50V 10% X7R 0402 0402B103K500CT VDD <1mm; CAPC1005X60
C3: 10uF 35V 10% X5R 0805 GRM21BR6YA106KE43L VDD; CAPC2012X110
C4: 10nF 50V 10% X7R 0402 0402B103K500CT VISOOUT <1mm; CAPC1005X60
C5: 10uF 35V 10% X5R 0805 GRM21BR6YA106KE43L VISOOUT; CAPC2012X110
C6: 100nF 16V 10% X7R 0402 CL05B104KO5NNNC VISOIN; CAPC1005X60
C8: 1uF 50V 10% X5R 0603 CL10A105KB8NNNC VDD 2-4mm; CAPC1608X85
C9: 1uF 50V 10% X5R 0603 CL10A105KB8NNNC VISOOUT 2-4mm; CAPC1608X85
D1: SM712.TCT; SOT23_
FB1, FB2: BLM15EX331SN1D; INDC1006X60N
J1: JST XH B4B-XH-A DMX: COM,-,+,SHELL; B4B-XH-A
L1: ACT45B-510-2P-TL003 - DNP; ACT45B_4P5X3P2
R1: 100k 1% 0.063W 0402 Yageo RC0402FR-07100KL; RESC1005X40
R2, R3: 10k 1% 0.063W 0402 Yageo RC0402FR-0710KL; RESC1005X40
R10, R11: 0R 5% 0.063W 0402 Yageo RC0402JR-070RL CMC BYPASS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; RESC1005X40
U2: ISOW1412DFMR; DFM0020A_TI

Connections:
DMX_DATA_MINUS: D1.2 (IO2), J1.2, L1.3 (B2), R11.2
DMX_DATA_PLUS: D1.1 (IO1), J1.3, L1.2 (A2), R10.2
DMX_DIR_GPIO4: R2.1, U2.3 (DE), U2.5 (RE_N); also elsewhere on the board
DMX_RX_GPIO6: U2.4 (R); also elsewhere on the board
DMX_TRX_MINUS: L1.4 (B1), R11.1, U2.18 (Z), U2.19 (B)
DMX_TRX_PLUS: L1.1 (A1), R10.1, U2.17 (Y), U2.20 (A)
DMX_TX_GPIO2: R1.2, U2.2 (D); also elsewhere on the board
GND_DMX_CONVERTER: C4.2, C5.2, C9.2, FB2.1, U2.11 (GND2)
GND_DMX_ISO: C6.2, D1.3 (GND), FB2.2, J1.1, U2.15 (GISOIN)
GND_LOGIC: C1.2, C2.2, C3.2, C8.2, R2.2, U2.6 (GNDIO), U2.10 (GND1); also elsewhere on the board
ISOW_EN_FLT: R3.2, U2.8 (EN_FLT); also elsewhere on the board
VCC_3V3_LOGIC: C1.1, R1.1, R3.1, U2.1 (VIO); also elsewhere on the board
VCC_5V_DMX_ISO: C6.1, FB1.2, U2.16 (VISOIN)
VDD_5V_ISOW_FUSED: C2.1, C3.1, C8.1, U2.9 (VDD); also elsewhere on the board
VISO_5V_CONVERTER: C4.1, C5.1, C9.1, FB1.1, U2.12 (VISOOUT), U2.13 (MODE)
XLR_SHELL: J1.4

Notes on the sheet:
WiFiPicoDMX Rev. A — Reinforced-isolated DMX/RDM output
Default: FIT R10/R11 (0R), DNP L1. L1 option is TDK ACT45B-510-2P-TL003; fit it only after EMC/signal-integrity testing.
No permanent 120R termination: terminate only at the far end of the DMX cable.
Keep GND_LOGIC and GND_DMX_ISO separate. Preserve TI isolation keep-outs and place bypass parts per TI layout.
J1 pad order: P1 DMX COM/XLR1, P2 DMX-/XLR2, P3 DMX+/XLR3, P4 shell. Panel connector is wired, not PCB-mounted.

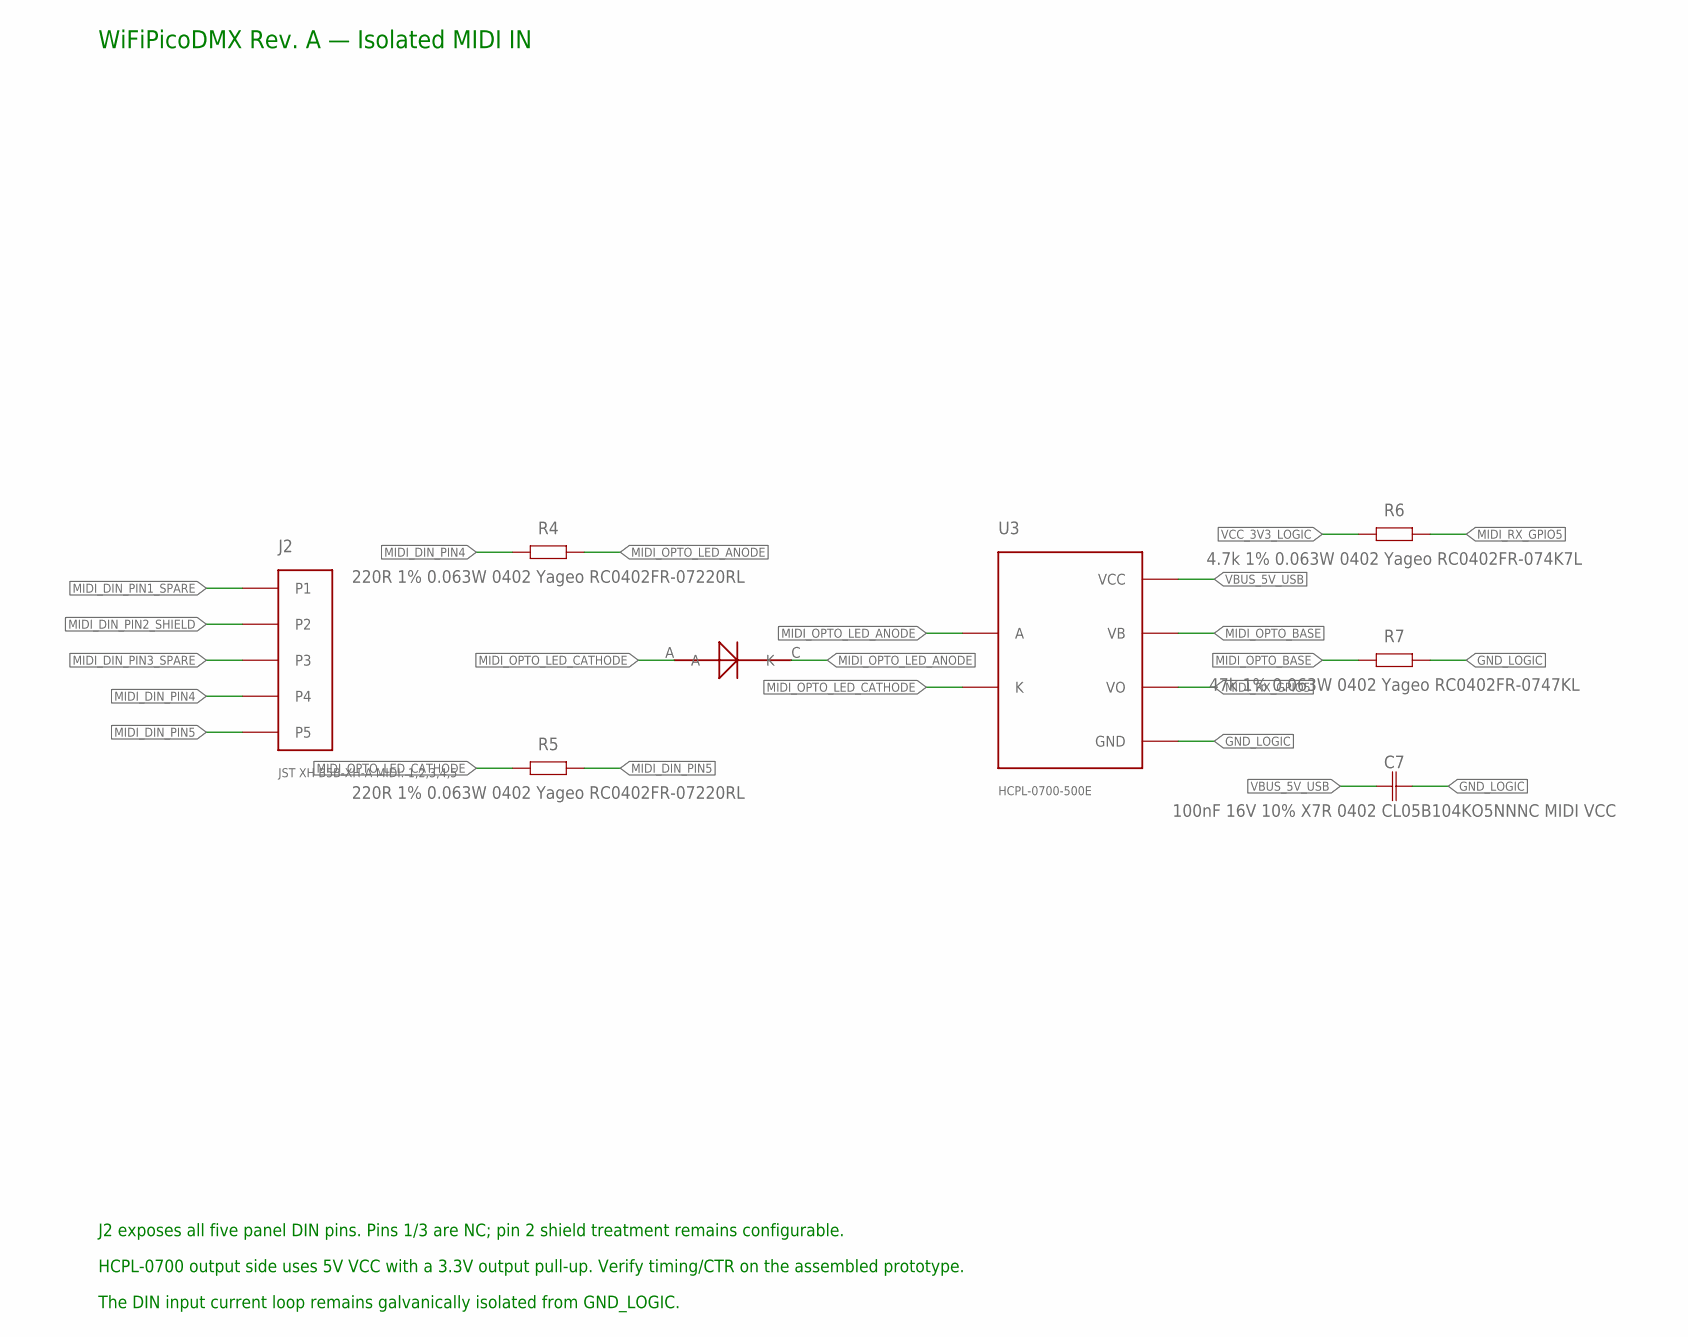
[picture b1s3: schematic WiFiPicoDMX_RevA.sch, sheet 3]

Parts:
C7: 100nF 16V 10% X7R 0402 CL05B104KO5NNNC MIDI VCC; CAPC1005X60
D2: 1N4148WS-E3-08; SOD323_VISHAY
J2: JST XH B5B-XH-A MIDI: 1,2,3,4,5; B5B-XH-A
R4, R5: 220R 1% 0.063W 0402 Yageo RC0402FR-07220RL; RESC1005X40
R6: 4.7k 1% 0.063W 0402 Yageo RC0402FR-074K7L; RESC1005X40
R7: 47k 1% 0.063W 0402 Yageo RC0402FR-0747KL; RESC1005X40
U3: HCPL-0700-500E; HCPL0700_SO8

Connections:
GND_LOGIC: C7.2, R7.2, U3.5 (GND); also elsewhere on the board
MIDI_DIN_PIN1_SPARE: J2.1
MIDI_DIN_PIN2_SHIELD: J2.2
MIDI_DIN_PIN3_SPARE: J2.3
MIDI_DIN_PIN4: J2.4, R4.1
MIDI_DIN_PIN5: J2.5, R5.2
MIDI_OPTO_BASE: R7.1, U3.7 (VB)
MIDI_OPTO_LED_ANODE: D2.C (K), R4.2, U3.2 (A)
MIDI_OPTO_LED_CATHODE: D2.A, R5.1, U3.3 (K)
MIDI_RX_GPIO5: R6.2, U3.6 (VO); also elsewhere on the board
VBUS_5V_USB: C7.1, U3.8 (VCC); also elsewhere on the board
VCC_3V3_LOGIC: R6.1; also elsewhere on the board

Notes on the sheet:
WiFiPicoDMX Rev. A — Isolated MIDI IN
J2 exposes all five panel DIN pins. Pins 1/3 are NC; pin 2 shield treatment remains configurable.
HCPL-0700 output side uses 5V VCC with a 3.3V output pull-up. Verify timing/CTR on the assembled prototype.
The DIN input current loop remains galvanically isolated from GND_LOGIC.

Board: 2 copper layers, 37 parts (0 on the bottom side), 49 nets, no tracks yet.
